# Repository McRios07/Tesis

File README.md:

# Tesis
Repositorio de los archivos de matlab y python de la maestría

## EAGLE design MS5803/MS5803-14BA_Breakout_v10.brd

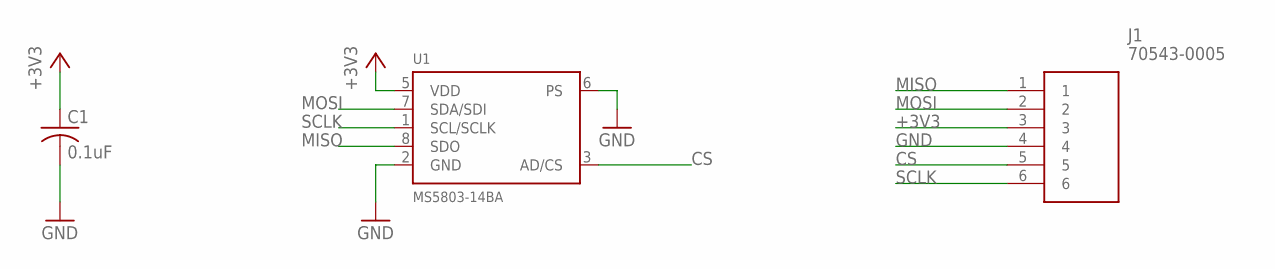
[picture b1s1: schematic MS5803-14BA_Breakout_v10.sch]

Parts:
C1: 0.1uF; C1206
J1: 70543-0005; SHDR6W117P0X254_1X6_1779X508X1
U1: MS5803-14BA; MS5803

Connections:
+3V3: C1.1, J1.3, U1.5 (VDD)
CS: J1.5, U1.3 (AD/CS)
GND: C1.2, J1.4, U1.2 (GND), U1.6 (PS)
MISO: J1.1, U1.8 (SDO)
MOSI: J1.2, U1.7 (SDA/SDI)
SCLK: J1.6, U1.1 (SCL/SCLK)

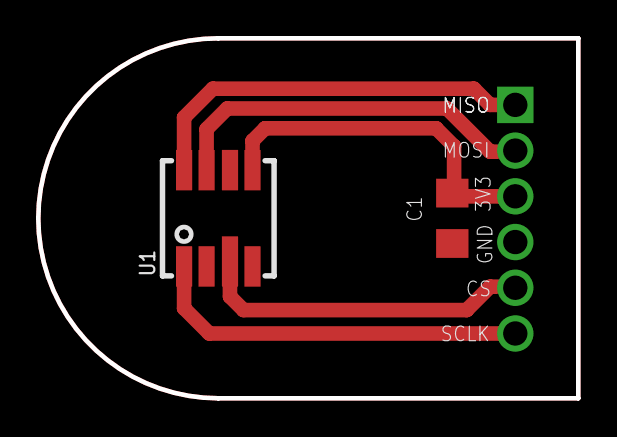
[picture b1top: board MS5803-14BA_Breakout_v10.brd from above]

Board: 2 copper layers, 30.0 x 20.0 mm, 3 parts (1 on the bottom side), 6 nets.

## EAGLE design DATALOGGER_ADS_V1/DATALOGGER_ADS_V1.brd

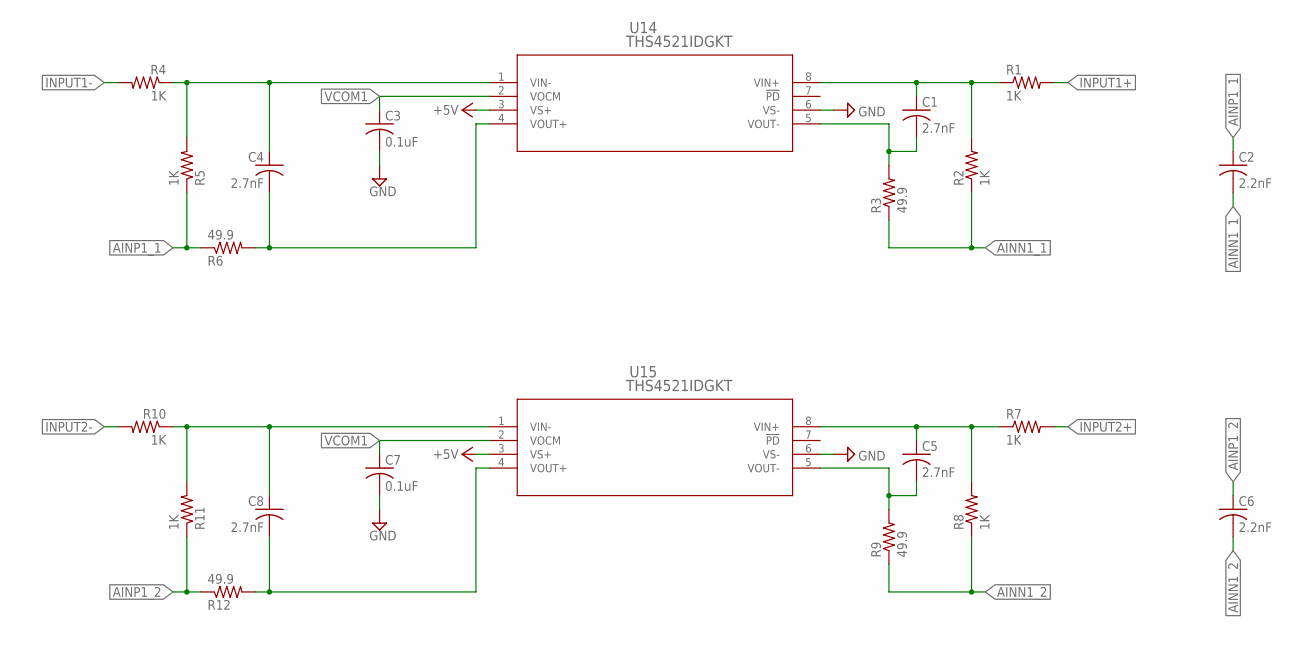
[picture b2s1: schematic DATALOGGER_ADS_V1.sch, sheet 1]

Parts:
C1, C4, C5, C8: 2.7nF; C0603
C2, C6: 2.2nF; C0603
C3, C7: 0.1uF; C0603
R1, R2, R4, R5, R7, R8, R10, R11: 1K; R0603
R3, R6, R9, R12: 49.9; R0603
U14, U15: THS4521IDGKT; DGK8

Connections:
+5V: U14.3 (VS+), U15.3 (VS+); also elsewhere on the board
AINN1_1: C2.2, R2.1, R3.1; also elsewhere on the board
AINN1_2: C6.2, R8.1, R9.1; also elsewhere on the board
AINP1_1: C2.1, R5.1, R6.1; also elsewhere on the board
AINP1_2: C6.1, R11.1, R12.1; also elsewhere on the board
GND: C3.2, C7.2, U14.6 (VS-), U15.6 (VS-); also elsewhere on the board
INPUT1+: R1.2; also elsewhere on the board
INPUT1-: R4.2; also elsewhere on the board
INPUT2+: R7.2; also elsewhere on the board
INPUT2-: R10.2; also elsewhere on the board
unnamed: C4.1, R4.1, R5.2, U14.1 (VIN-)
unnamed: C1.1, R1.1, R2.2, U14.8 (VIN+)
unnamed: C1.2, R3.2, U14.5 (VOUT-)
unnamed: C4.2, R6.2, U14.4 (VOUT+)
unnamed: C5.1, R7.1, R8.2, U15.8 (VIN+)
unnamed: C5.2, R9.2, U15.5 (VOUT-)
unnamed: C8.1, R10.1, R11.2, U15.1 (VIN-)
unnamed: C8.2, R12.2, U15.4 (VOUT+)
VCOM1: C3.1, C7.1, U14.2 (VOCM), U15.2 (VOCM); also elsewhere on the board

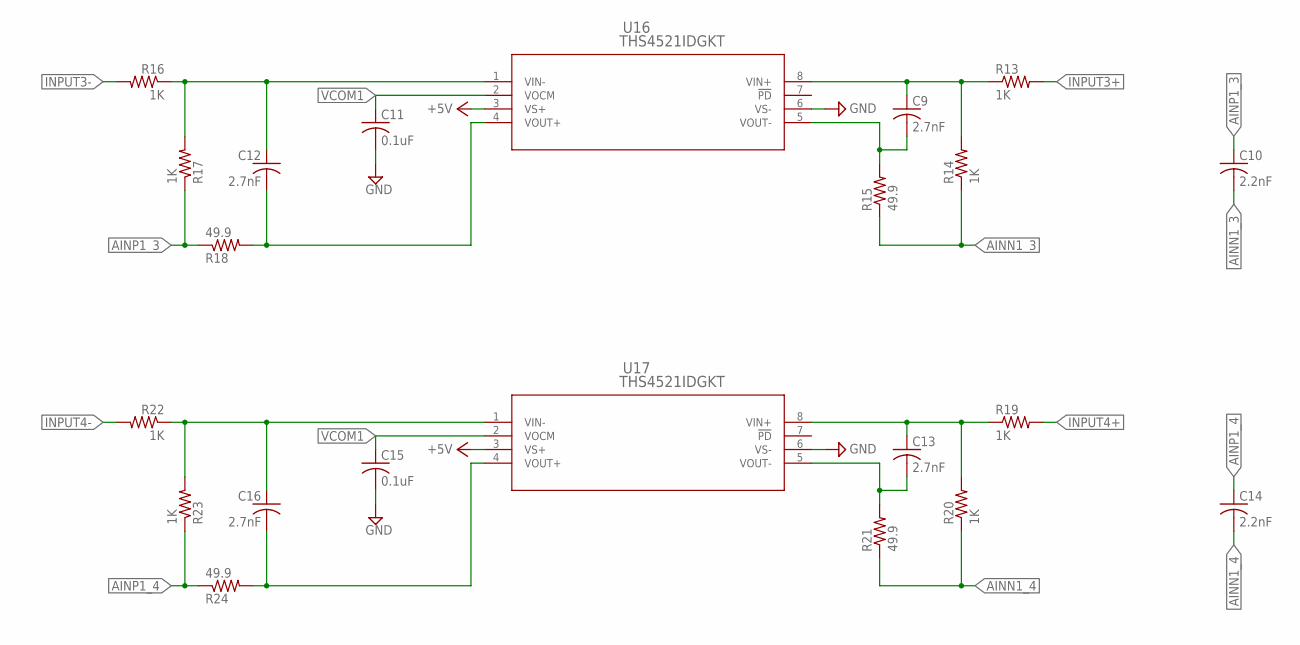
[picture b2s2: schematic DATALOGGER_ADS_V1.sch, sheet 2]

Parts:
C9, C12, C13, C16: 2.7nF; C0603
C10, C14: 2.2nF; C0603
C11, C15: 0.1uF; C0603
R13, R14, R16, R17, R19, R20, R22, R23: 1K; R0603
R15, R18, R21, R24: 49.9; R0603
U16, U17: THS4521IDGKT; DGK8

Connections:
+5V: U16.3 (VS+), U17.3 (VS+); also elsewhere on the board
AINN1_3: C10.2, R14.1, R15.1; also elsewhere on the board
AINN1_4: C14.2, R20.1, R21.1; also elsewhere on the board
AINP1_3: C10.1, R17.1, R18.1; also elsewhere on the board
AINP1_4: C14.1, R23.1, R24.1; also elsewhere on the board
GND: C11.2, C15.2, U16.6 (VS-), U17.6 (VS-); also elsewhere on the board
INPUT3+: R13.2; also elsewhere on the board
INPUT3-: R16.2; also elsewhere on the board
INPUT4+: R19.2; also elsewhere on the board
INPUT4-: R22.2; also elsewhere on the board
unnamed: C9.1, R13.1, R14.2, U16.8 (VIN+)
unnamed: C9.2, R15.2, U16.5 (VOUT-)
unnamed: C12.1, R16.1, R17.2, U16.1 (VIN-)
unnamed: C12.2, R18.2, U16.4 (VOUT+)
unnamed: C13.1, R19.1, R20.2, U17.8 (VIN+)
unnamed: C13.2, R21.2, U17.5 (VOUT-)
unnamed: C16.1, R22.1, R23.2, U17.1 (VIN-)
unnamed: C16.2, R24.2, U17.4 (VOUT+)
VCOM1: C11.1, C15.1, U16.2 (VOCM), U17.2 (VOCM); also elsewhere on the board

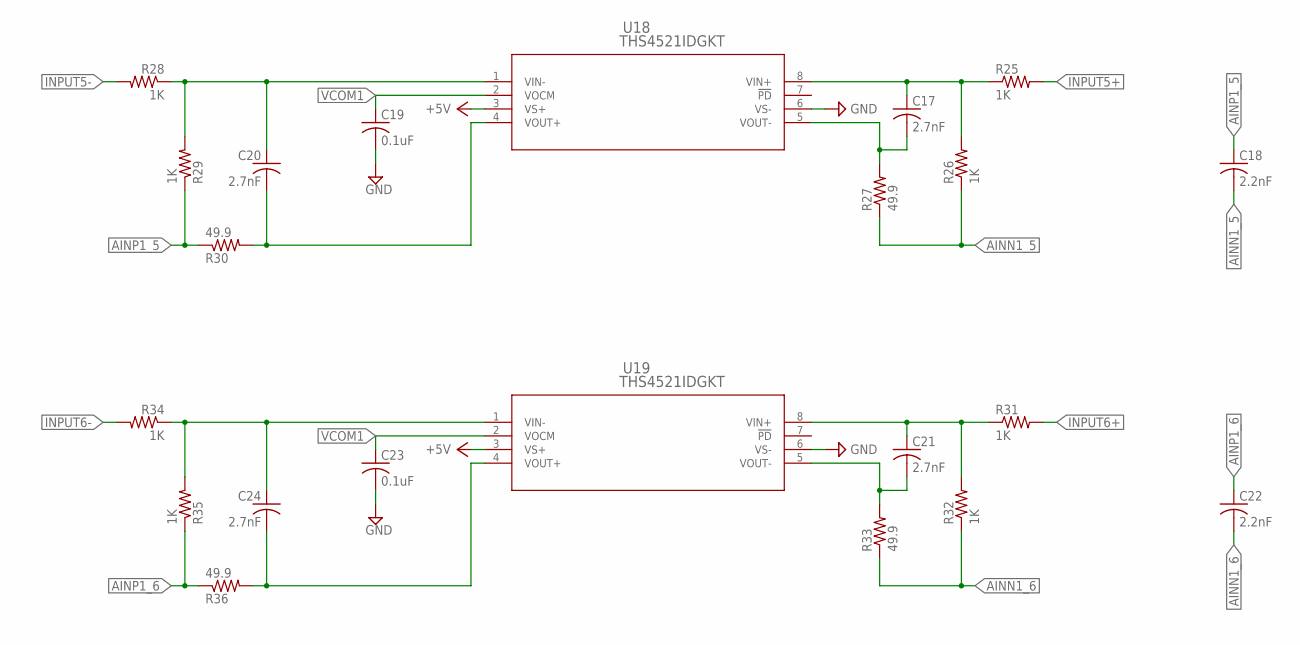
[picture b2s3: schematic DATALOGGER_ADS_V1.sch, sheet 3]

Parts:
C17, C20, C21, C24: 2.7nF; C0603
C18, C22: 2.2nF; C0603
C19, C23: 0.1uF; C0603
R25, R26, R28, R29, R31, R32, R34, R35: 1K; R0603
R27, R30, R33, R36: 49.9; R0603
U18, U19: THS4521IDGKT; DGK8

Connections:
+5V: U18.3 (VS+), U19.3 (VS+); also elsewhere on the board
AINN1_5: C18.2, R26.1, R27.1; also elsewhere on the board
AINN1_6: C22.2, R32.1, R33.1; also elsewhere on the board
AINP1_5: C18.1, R29.1, R30.1; also elsewhere on the board
AINP1_6: C22.1, R35.1, R36.1; also elsewhere on the board
GND: C19.2, C23.2, U18.6 (VS-), U19.6 (VS-); also elsewhere on the board
INPUT5+: R25.2; also elsewhere on the board
INPUT5-: R28.2; also elsewhere on the board
INPUT6+: R31.2; also elsewhere on the board
INPUT6-: R34.2; also elsewhere on the board
unnamed: C17.1, R25.1, R26.2, U18.8 (VIN+)
unnamed: C17.2, R27.2, U18.5 (VOUT-)
unnamed: C20.1, R28.1, R29.2, U18.1 (VIN-)
unnamed: C20.2, R30.2, U18.4 (VOUT+)
unnamed: C21.1, R31.1, R32.2, U19.8 (VIN+)
unnamed: C21.2, R33.2, U19.5 (VOUT-)
unnamed: C24.1, R34.1, R35.2, U19.1 (VIN-)
unnamed: C24.2, R36.2, U19.4 (VOUT+)
VCOM1: C19.1, C23.1, U18.2 (VOCM), U19.2 (VOCM); also elsewhere on the board

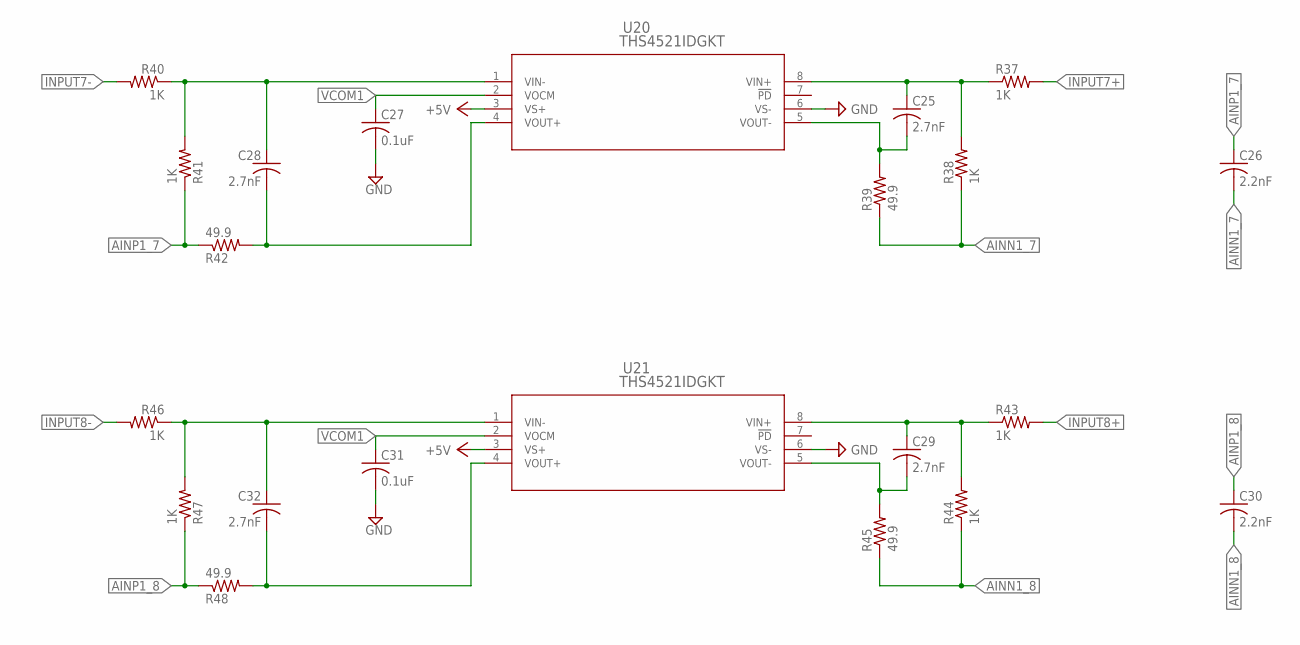
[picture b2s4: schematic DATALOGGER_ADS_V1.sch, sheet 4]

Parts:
C25, C28, C29, C32: 2.7nF; C0603
C26, C30: 2.2nF; C0603
C27, C31: 0.1uF; C0603
R37, R38, R40, R41, R43, R44, R46, R47: 1K; R0603
R39, R42, R45, R48: 49.9; R0603
U20, U21: THS4521IDGKT; DGK8

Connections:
+5V: U20.3 (VS+), U21.3 (VS+); also elsewhere on the board
AINN1_7: C26.2, R38.1, R39.1; also elsewhere on the board
AINN1_8: C30.2, R44.1, R45.1; also elsewhere on the board
AINP1_7: C26.1, R41.1, R42.1; also elsewhere on the board
AINP1_8: C30.1, R47.1, R48.1; also elsewhere on the board
GND: C27.2, C31.2, U20.6 (VS-), U21.6 (VS-); also elsewhere on the board
INPUT7+: R37.2; also elsewhere on the board
INPUT7-: R40.2; also elsewhere on the board
INPUT8+: R43.2; also elsewhere on the board
INPUT8-: R46.2; also elsewhere on the board
unnamed: C25.1, R37.1, R38.2, U20.8 (VIN+)
unnamed: C25.2, R39.2, U20.5 (VOUT-)
unnamed: C28.1, R40.1, R41.2, U20.1 (VIN-)
unnamed: C28.2, R42.2, U20.4 (VOUT+)
unnamed: C29.1, R43.1, R44.2, U21.8 (VIN+)
unnamed: C29.2, R45.2, U21.5 (VOUT-)
unnamed: C32.1, R46.1, R47.2, U21.1 (VIN-)
unnamed: C32.2, R48.2, U21.4 (VOUT+)
VCOM1: C27.1, C31.1, U20.2 (VOCM), U21.2 (VOCM); also elsewhere on the board

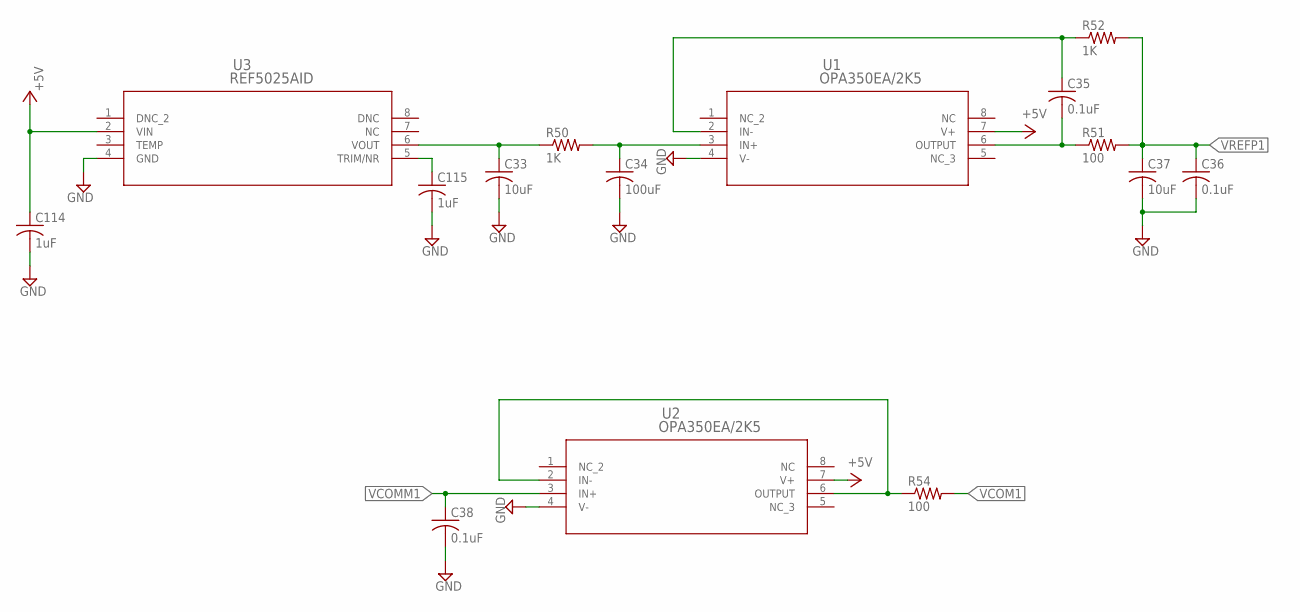
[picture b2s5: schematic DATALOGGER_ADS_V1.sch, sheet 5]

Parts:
C33, C37: 10uF; C0603
C34: 100uF; C1206
C35, C36, C38: 0.1uF; C0603
C114, C115: 1uF; C0603
R50, R52: 1K; R0603
R51, R54: 100; R0603
U1, U2: OPA350EA/2K5; DGK8_TEX
U3: REF5025AID; D8

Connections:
+5V: C114.1, U1.7 (V+), U2.7 (V+), U3.2 (VIN); also elsewhere on the board
GND: C33.2, C34.2, C36.2, C37.2, C38.2, C114.2, C115.2, U1.4 (V-), U2.4 (V-), U3.4 (GND); also elsewhere on the board
unnamed: C34.1, R50.2, U1.3 (IN+)
unnamed: C115.1, U3.5 (TRIM/NR)
unnamed: C33.1, R50.1, U3.6 (VOUT)
unnamed: C35.1, R52.1, U1.2 (IN-)
unnamed: C35.2, R51.1, U1.6 (OUTPUT)
unnamed: R54.1, U2.2 (IN-), U2.6 (OUTPUT)
VCOM1: R54.2; also elsewhere on the board
VCOMM1: C38.1, U2.3 (IN+); also elsewhere on the board
VREFP1: C36.1, C37.1, R51.2, R52.2; also elsewhere on the board

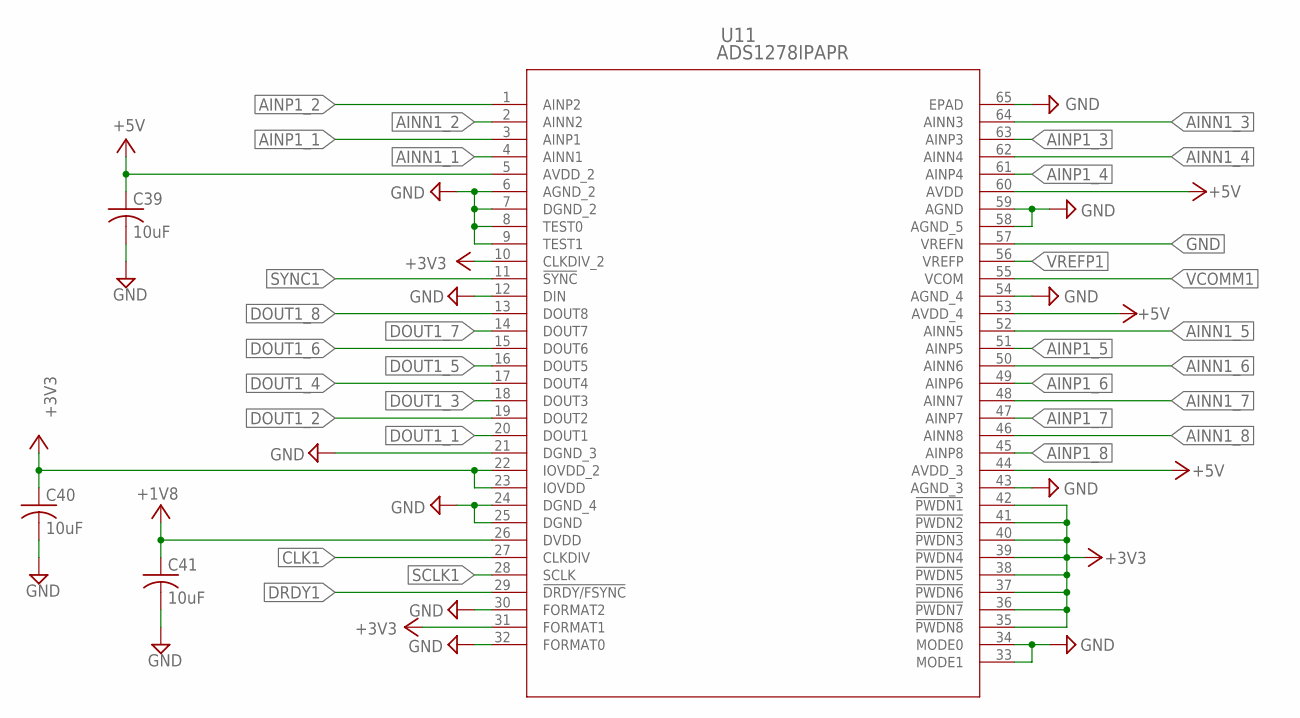
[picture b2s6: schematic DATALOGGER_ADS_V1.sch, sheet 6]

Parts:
C39, C40, C41: 10uF; C0603
U11: ADS1278IPAPR; PAP64_7X7

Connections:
+1V8: C41.1, U11.26 (DVDD); also elsewhere on the board
+3V3: C40.1, U11.10 (CLKDIV_2), U11.22 (IOVDD_2), U11.23 (IOVDD), U11.31 (FORMAT1), U11.35 (!PWDN8), U11.36 (!PWDN7), U11.37 (!PWDN6), U11.38 (!PWDN5), U11.39 (!PWDN4), U11.40 (!PWDN3), U11.41 (!PWDN2), U11.42 (!PWDN1); also elsewhere on the board
+5V: C39.1, U11.5 (AVDD_2), U11.44 (AVDD_3), U11.53 (AVDD_4), U11.60 (AVDD); also elsewhere on the board
AINN1_1: U11.4 (AINN1); also elsewhere on the board
AINN1_2: U11.2 (AINN2); also elsewhere on the board
AINN1_3: U11.64 (AINN3); also elsewhere on the board
AINN1_4: U11.62 (AINN4); also elsewhere on the board
AINN1_5: U11.52 (AINN5); also elsewhere on the board
AINN1_6: U11.50 (AINN6); also elsewhere on the board
AINN1_7: U11.48 (AINN7); also elsewhere on the board
AINN1_8: U11.46 (AINN8); also elsewhere on the board
AINP1_1: U11.3 (AINP1); also elsewhere on the board
AINP1_2: U11.1 (AINP2); also elsewhere on the board
AINP1_3: U11.63 (AINP3); also elsewhere on the board
AINP1_4: U11.61 (AINP4); also elsewhere on the board
AINP1_5: U11.51 (AINP5); also elsewhere on the board
AINP1_6: U11.49 (AINP6); also elsewhere on the board
AINP1_7: U11.47 (AINP7); also elsewhere on the board
AINP1_8: U11.45 (AINP8); also elsewhere on the board
CLK1: U11.27 (CLKDIV); also elsewhere on the board
DOUT1_1: U11.20 (DOUT1); also elsewhere on the board
DOUT1_2: U11.19 (DOUT2); also elsewhere on the board
DOUT1_3: U11.18 (DOUT3); also elsewhere on the board
DOUT1_4: U11.17 (DOUT4); also elsewhere on the board
DOUT1_5: U11.16 (DOUT5); also elsewhere on the board
DOUT1_6: U11.15 (DOUT6); also elsewhere on the board
DOUT1_7: U11.14 (DOUT7); also elsewhere on the board
DOUT1_8: U11.13 (DOUT8); also elsewhere on the board
DRDY1: U11.29 (!DRDY/FSYNC); also elsewhere on the board
GND: C39.2, C40.2, C41.2, U11.6 (AGND_2), U11.7 (DGND_2), U11.8 (TEST0), U11.9 (TEST1), U11.12 (DIN), U11.21 (DGND_3), U11.24 (DGND_4), U11.25 (DGND), U11.30 (FORMAT2), U11.32 (FORMAT0), U11.33 (MODE1), U11.34 (MODE0), U11.43 (AGND_3), U11.54 (AGND_4), U11.57 (VREFN), U11.58 (AGND_5), U11.59 (AGND), U11.65 (EPAD); also elsewhere on the board
SCLK1: U11.28 (SCLK); also elsewhere on the board
SYNC1: U11.11 (!SYNC); also elsewhere on the board
VCOMM1: U11.55 (VCOM); also elsewhere on the board
VREFP1: U11.56 (VREFP); also elsewhere on the board

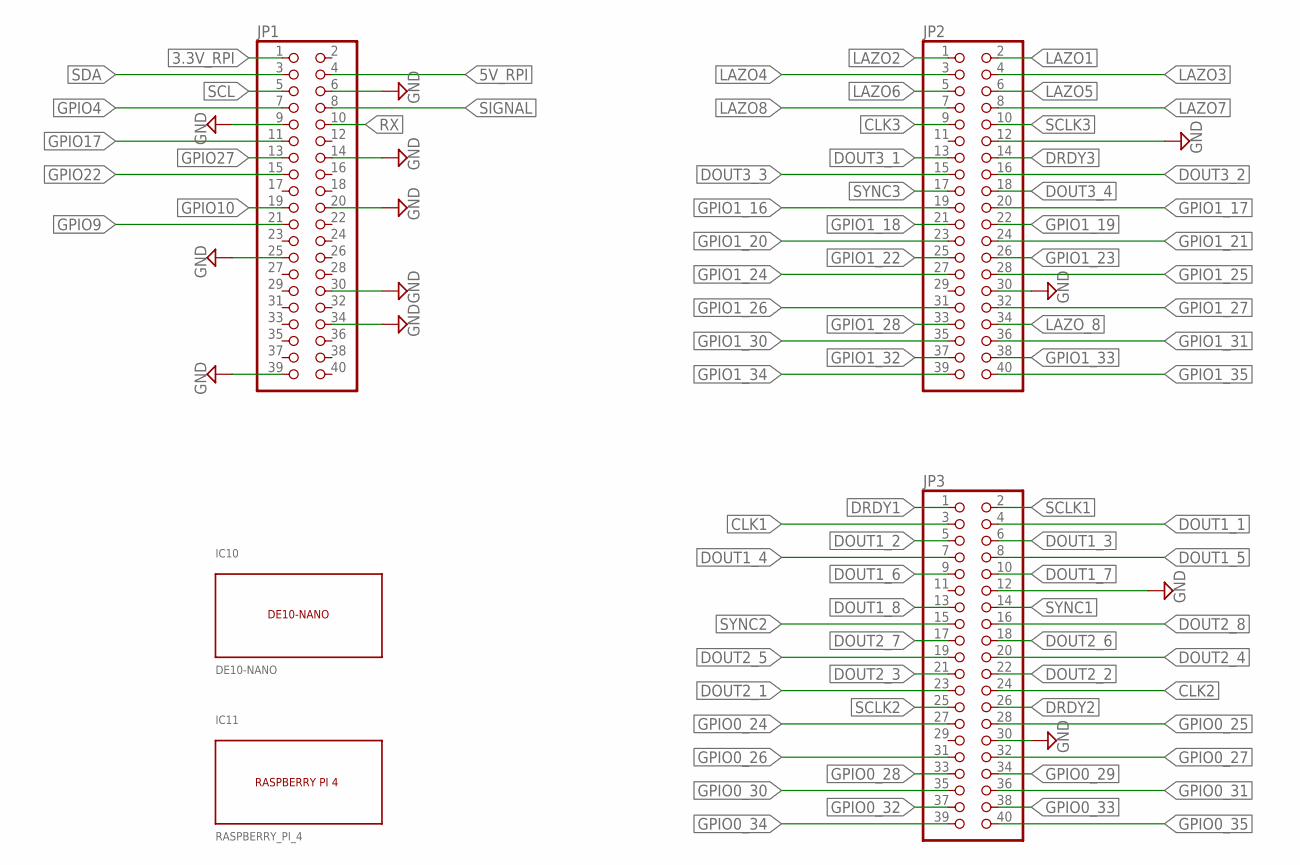
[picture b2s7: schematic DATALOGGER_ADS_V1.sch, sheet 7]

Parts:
IC10: DE10-NANO; DE10_NANO
IC11: RASPBERRY_PI_4
JP1, JP2, JP3: PINHD-2X20; 2X20

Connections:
3.3V_RPI: JP1.1; also elsewhere on the board
5V_RPI: JP1.4; also elsewhere on the board
CLK1: JP3.3; also elsewhere on the board
CLK2: JP3.24; also elsewhere on the board
CLK3: JP2.9; also elsewhere on the board
DOUT1_1: JP3.4; also elsewhere on the board
DOUT1_2: JP3.5; also elsewhere on the board
DOUT1_3: JP3.6; also elsewhere on the board
DOUT1_4: JP3.7; also elsewhere on the board
DOUT1_5: JP3.8; also elsewhere on the board
DOUT1_6: JP3.9; also elsewhere on the board
DOUT1_7: JP3.10; also elsewhere on the board
DOUT1_8: JP3.13; also elsewhere on the board
DOUT2_1: JP3.23; also elsewhere on the board
DOUT2_2: JP3.22; also elsewhere on the board
DOUT2_3: JP3.21; also elsewhere on the board
DOUT2_4: JP3.20; also elsewhere on the board
DOUT2_5: JP3.19; also elsewhere on the board
DOUT2_6: JP3.18; also elsewhere on the board
DOUT2_7: JP3.17; also elsewhere on the board
DOUT2_8: JP3.16; also elsewhere on the board
DOUT3_1: JP2.13; also elsewhere on the board
DOUT3_2: JP2.16; also elsewhere on the board
DOUT3_3: JP2.15; also elsewhere on the board
DOUT3_4: JP2.18; also elsewhere on the board
DRDY1: JP3.1; also elsewhere on the board
DRDY2: JP3.26; also elsewhere on the board
DRDY3: JP2.14; also elsewhere on the board
GND: JP1.6, JP1.9, JP1.14, JP1.20, JP1.25, JP1.30, JP1.34, JP1.39, JP2.12, JP2.30, JP3.12, JP3.30; also elsewhere on the board
GPIO0_24: JP3.27
GPIO0_25: JP3.28
GPIO0_26: JP3.31
GPIO0_27: JP3.32
GPIO0_28: JP3.33
GPIO0_29: JP3.34
GPIO0_30: JP3.35
GPIO0_31: JP3.36
GPIO0_32: JP3.37
GPIO0_33: JP3.38
GPIO0_34: JP3.39
GPIO0_35: JP3.40
GPIO1_16: JP2.19
GPIO1_17: JP2.20
GPIO1_18: JP2.21
GPIO1_19: JP2.22
GPIO1_20: JP2.23
GPIO1_21: JP2.24
GPIO1_22: JP2.25
GPIO1_23: JP2.26
GPIO1_24: JP2.27
GPIO1_25: JP2.28
GPIO1_26: JP2.31
GPIO1_27: JP2.32
GPIO1_28: JP2.33
GPIO1_30: JP2.35
GPIO1_31: JP2.36
GPIO1_32: JP2.37
GPIO1_33: JP2.38
GPIO1_34: JP2.39
GPIO1_35: JP2.40
GPIO4: JP1.7; also elsewhere on the board
GPIO9: JP1.21
GPIO10: JP1.19
GPIO17: JP1.11; also elsewhere on the board
GPIO22: JP1.15; also elsewhere on the board
GPIO27: JP1.13; also elsewhere on the board
LAZO1: JP2.2; also elsewhere on the board
LAZO2: JP2.1; also elsewhere on the board
LAZO3: JP2.4; also elsewhere on the board
LAZO4: JP2.3; also elsewhere on the board
LAZO5: JP2.6; also elsewhere on the board
LAZO6: JP2.5; also elsewhere on the board
LAZO7: JP2.8; also elsewhere on the board
LAZO8: JP2.7; also elsewhere on the board
LAZO_8: JP2.34
RX: JP1.10
SCL: JP1.5; also elsewhere on the board
SCLK1: JP3.2; also elsewhere on the board
SCLK2: JP3.25; also elsewhere on the board
SCLK3: JP2.10; also elsewhere on the board
SDA: JP1.3; also elsewhere on the board
SIGNAL: JP1.8; also elsewhere on the board
SYNC1: JP3.14; also elsewhere on the board
SYNC2: JP3.15; also elsewhere on the board
SYNC3: JP2.17; also elsewhere on the board

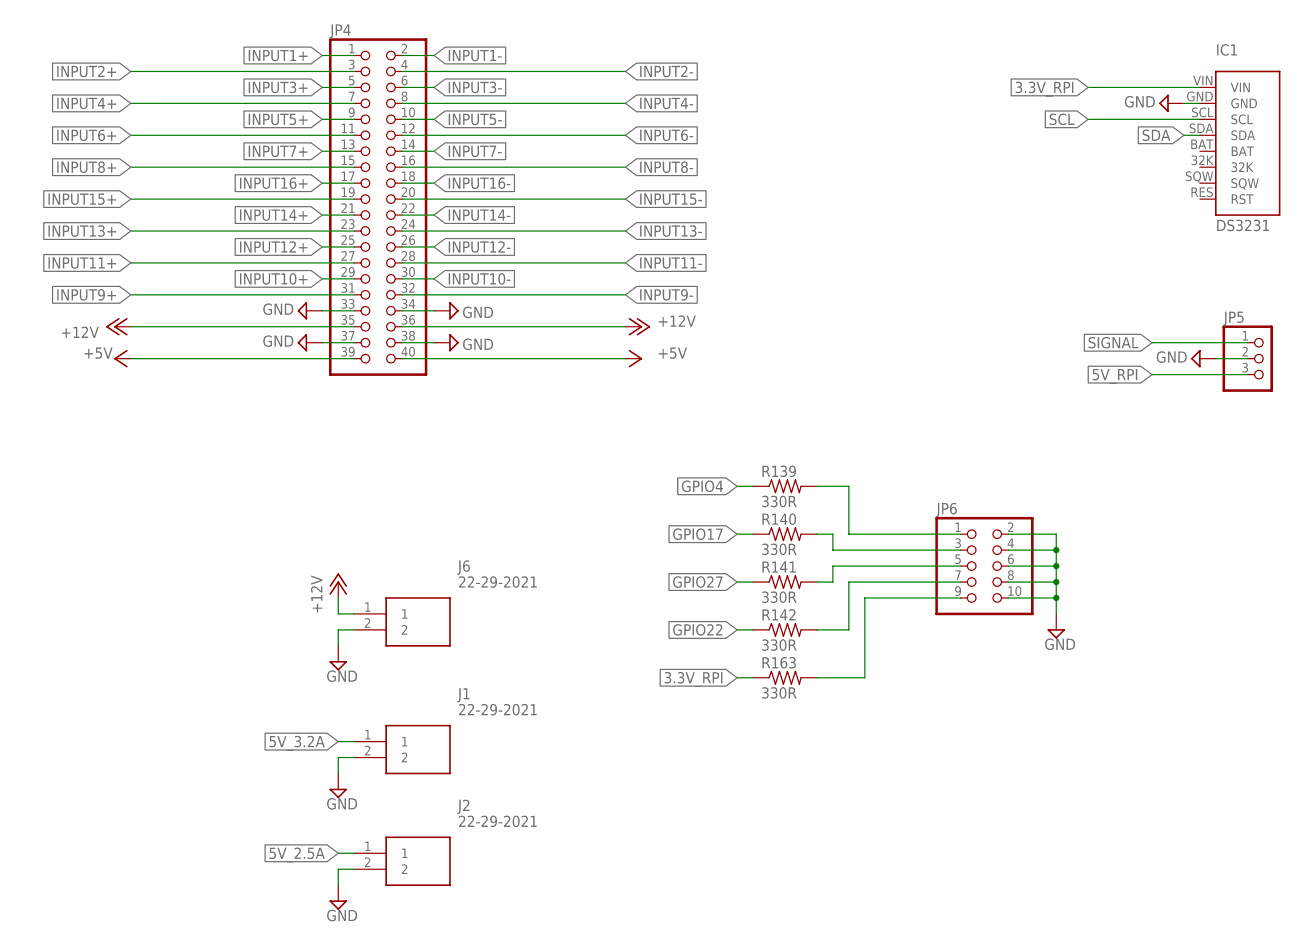
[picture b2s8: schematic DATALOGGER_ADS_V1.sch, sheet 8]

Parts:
IC1: DS3231
J1, J2, J6: 22-29-2021; SHDR2W64P0X254_1X2_508X580X117
JP4: PINHD-2X20; 2X20
JP5: PINHD-1X3; 1X03
JP6: PINHD-2X5; 2X05
R139, R140, R141, R142, R163: 330R; R0603

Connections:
3.3V_RPI: IC1.VIN, R163.1; also elsewhere on the board
5V_2.5A: J2.1; also elsewhere on the board
5V_3.2A: J1.1; also elsewhere on the board
5V_RPI: JP5.3; also elsewhere on the board
+5V: JP4.39, JP4.40; also elsewhere on the board
+12V: J6.1, JP4.35, JP4.36; also elsewhere on the board
GND: IC1.GND, J1.2, J2.2, J6.2, JP4.33, JP4.34, JP4.37, JP4.38, JP5.2, JP6.2, JP6.4, JP6.6, JP6.8, JP6.10; also elsewhere on the board
GPIO4: R139.1; also elsewhere on the board
GPIO17: R140.1; also elsewhere on the board
GPIO22: R142.1; also elsewhere on the board
GPIO27: R141.1; also elsewhere on the board
INPUT1+: JP4.1; also elsewhere on the board
INPUT1-: JP4.2; also elsewhere on the board
INPUT2+: JP4.3; also elsewhere on the board
INPUT2-: JP4.4; also elsewhere on the board
INPUT3+: JP4.5; also elsewhere on the board
INPUT3-: JP4.6; also elsewhere on the board
INPUT4+: JP4.7; also elsewhere on the board
INPUT4-: JP4.8; also elsewhere on the board
INPUT5+: JP4.9; also elsewhere on the board
INPUT5-: JP4.10; also elsewhere on the board
INPUT6+: JP4.11; also elsewhere on the board
INPUT6-: JP4.12; also elsewhere on the board
INPUT7+: JP4.13; also elsewhere on the board
INPUT7-: JP4.14; also elsewhere on the board
INPUT8+: JP4.15; also elsewhere on the board
INPUT8-: JP4.16; also elsewhere on the board
INPUT9+: JP4.31; also elsewhere on the board
INPUT9-: JP4.32; also elsewhere on the board
INPUT10+: JP4.29; also elsewhere on the board
INPUT10-: JP4.30; also elsewhere on the board
INPUT11+: JP4.27; also elsewhere on the board
INPUT11-: JP4.28; also elsewhere on the board
INPUT12+: JP4.25; also elsewhere on the board
INPUT12-: JP4.26; also elsewhere on the board
INPUT13+: JP4.23; also elsewhere on the board
INPUT13-: JP4.24; also elsewhere on the board
INPUT14+: JP4.21; also elsewhere on the board
INPUT14-: JP4.22; also elsewhere on the board
INPUT15+: JP4.19; also elsewhere on the board
INPUT15-: JP4.20; also elsewhere on the board
INPUT16+: JP4.17; also elsewhere on the board
INPUT16-: JP4.18; also elsewhere on the board
unnamed: JP6.9, R163.2
unnamed: JP6.1, R139.2
unnamed: JP6.3, R140.2
unnamed: JP6.5, R141.2
unnamed: JP6.7, R142.2
SCL: IC1.SCL; also elsewhere on the board
SDA: IC1.SDA; also elsewhere on the board
SIGNAL: JP5.1; also elsewhere on the board

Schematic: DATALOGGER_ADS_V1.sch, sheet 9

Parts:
C42, C45, C46, C49: 2.7nF; C0603
C43, C47: 2.2nF; C0603
C44, C48: 0.1uF; C0603
R55, R56, R58, R59, R61, R62, R64, R65: 1K; R0603
R57, R60, R63, R66: 49.9; R0603
U22, U23: THS4521IDGKT; DGK8

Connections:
+5V: U22.3 (VS+), U23.3 (VS+); also elsewhere on the board
AINN2_1: C43.2, R56.1, R57.1; also elsewhere on the board
AINN2_2: C47.2, R62.1, R63.1; also elsewhere on the board
AINP2_1: C43.1, R59.1, R60.1; also elsewhere on the board
AINP2_2: C47.1, R65.1, R66.1; also elsewhere on the board
GND: C44.2, C48.2, U22.6 (VS-), U23.6 (VS-); also elsewhere on the board
INPUT9+: R55.2; also elsewhere on the board
INPUT9-: R58.2; also elsewhere on the board
INPUT10+: R61.2; also elsewhere on the board
INPUT10-: R64.2; also elsewhere on the board
unnamed: C42.1, R55.1, R56.2, U22.8 (VIN+)
unnamed: C42.2, R57.2, U22.5 (VOUT-)
unnamed: C45.1, R58.1, R59.2, U22.1 (VIN-)
unnamed: C45.2, R60.2, U22.4 (VOUT+)
unnamed: C46.1, R61.1, R62.2, U23.8 (VIN+)
unnamed: C46.2, R63.2, U23.5 (VOUT-)
unnamed: C49.1, R64.1, R65.2, U23.1 (VIN-)
unnamed: C49.2, R66.2, U23.4 (VOUT+)
VCOM2: C44.1, C48.1, U22.2 (VOCM), U23.2 (VOCM); also elsewhere on the board

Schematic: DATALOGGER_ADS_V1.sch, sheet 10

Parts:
C50, C53, C54, C57: 2.7nF; C0603
C51, C55: 2.2nF; C0603
C52, C56: 0.1uF; C0603
R67, R68, R70, R71, R73, R74, R76, R77: 1K; R0603
R69, R72, R75, R78: 49.9; R0603
U24, U25: THS4521IDGKT; DGK8

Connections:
+5V: U24.3 (VS+), U25.3 (VS+); also elsewhere on the board
AINN2_3: C51.2, R68.1, R69.1; also elsewhere on the board
AINN2_4: C55.2, R74.1, R75.1; also elsewhere on the board
AINP2_3: C51.1, R71.1, R72.1; also elsewhere on the board
AINP2_4: C55.1, R77.1, R78.1; also elsewhere on the board
GND: C52.2, C56.2, U24.6 (VS-), U25.6 (VS-); also elsewhere on the board
INPUT11+: R67.2; also elsewhere on the board
INPUT11-: R70.2; also elsewhere on the board
INPUT12+: R73.2; also elsewhere on the board
INPUT12-: R76.2; also elsewhere on the board
unnamed: C50.1, R67.1, R68.2, U24.8 (VIN+)
unnamed: C50.2, R69.2, U24.5 (VOUT-)
unnamed: C53.1, R70.1, R71.2, U24.1 (VIN-)
unnamed: C53.2, R72.2, U24.4 (VOUT+)
unnamed: C54.1, R73.1, R74.2, U25.8 (VIN+)
unnamed: C54.2, R75.2, U25.5 (VOUT-)
unnamed: C57.1, R76.1, R77.2, U25.1 (VIN-)
unnamed: C57.2, R78.2, U25.4 (VOUT+)
VCOM2: C52.1, C56.1, U24.2 (VOCM), U25.2 (VOCM); also elsewhere on the board

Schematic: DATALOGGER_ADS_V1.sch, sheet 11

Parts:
C58, C61, C62, C65: 2.7nF; C0603
C59, C63: 2.2nF; C0603
C60, C64: 0.1uF; C0603
R79, R80, R82, R83, R85, R86, R88, R89: 1K; R0603
R81, R84, R87, R90: 49.9; R0603
U26, U27: THS4521IDGKT; DGK8

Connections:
+5V: U26.3 (VS+), U27.3 (VS+); also elsewhere on the board
AINN2_5: C59.2, R80.1, R81.1; also elsewhere on the board
AINN2_6: C63.2, R86.1, R87.1; also elsewhere on the board
AINP2_5: C59.1, R83.1, R84.1; also elsewhere on the board
AINP2_6: C63.1, R89.1, R90.1; also elsewhere on the board
GND: C60.2, C64.2, U26.6 (VS-), U27.6 (VS-); also elsewhere on the board
INPUT13+: R79.2; also elsewhere on the board
INPUT13-: R82.2; also elsewhere on the board
INPUT14+: R85.2; also elsewhere on the board
INPUT14-: R88.2; also elsewhere on the board
unnamed: C58.1, R79.1, R80.2, U26.8 (VIN+)
unnamed: C58.2, R81.2, U26.5 (VOUT-)
unnamed: C61.1, R82.1, R83.2, U26.1 (VIN-)
unnamed: C61.2, R84.2, U26.4 (VOUT+)
unnamed: C62.1, R85.1, R86.2, U27.8 (VIN+)
unnamed: C62.2, R87.2, U27.5 (VOUT-)
unnamed: C65.1, R88.1, R89.2, U27.1 (VIN-)
unnamed: C65.2, R90.2, U27.4 (VOUT+)
VCOM2: C60.1, C64.1, U26.2 (VOCM), U27.2 (VOCM); also elsewhere on the board

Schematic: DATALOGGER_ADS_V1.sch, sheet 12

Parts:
C66, C69, C70, C73: 2.7nF; C0603
C67, C71: 2.2nF; C0603
C68, C72: 0.1uF; C0603
R91, R92, R94, R95, R97, R98, R100, R101: 1K; R0603
R93, R96, R99, R102: 49.9; R0603
U28, U29: THS4521IDGKT; DGK8

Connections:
+5V: U28.3 (VS+), U29.3 (VS+); also elsewhere on the board
AINN2_7: C67.2, R92.1, R93.1; also elsewhere on the board
AINN2_8: C71.2, R98.1, R99.1; also elsewhere on the board
AINP2_7: C67.1, R95.1, R96.1; also elsewhere on the board
AINP2_8: C71.1, R101.1, R102.1; also elsewhere on the board
GND: C68.2, C72.2, U28.6 (VS-), U29.6 (VS-); also elsewhere on the board
INPUT15+: R91.2; also elsewhere on the board
INPUT15-: R94.2; also elsewhere on the board
INPUT16+: R97.2; also elsewhere on the board
INPUT16-: R100.2; also elsewhere on the board
unnamed: C66.1, R91.1, R92.2, U28.8 (VIN+)
unnamed: C66.2, R93.2, U28.5 (VOUT-)
unnamed: C69.1, R94.1, R95.2, U28.1 (VIN-)
unnamed: C69.2, R96.2, U28.4 (VOUT+)
unnamed: C70.1, R97.1, R98.2, U29.8 (VIN+)
unnamed: C70.2, R99.2, U29.5 (VOUT-)
unnamed: C73.1, R100.1, R101.2, U29.1 (VIN-)
unnamed: C73.2, R102.2, U29.4 (VOUT+)
VCOM2: C68.1, C72.1, U28.2 (VOCM), U29.2 (VOCM); also elsewhere on the board

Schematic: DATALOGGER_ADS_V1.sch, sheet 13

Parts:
C74, C78: 10uF; C0603
C75: 100uF; C1206
C76, C77, C79: 0.1uF; C0603
C118, C119: 1uF; C0603
R104, R106: 1K; R0603
R105, R108: 100; R0603
U4, U5: OPA350EA/2K5; DGK8_TEX
U13: REF5025AID; D8

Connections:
+5V: C119.1, U4.7 (V+), U5.7 (V+), U13.2 (VIN); also elsewhere on the board
GND: C74.2, C75.2, C77.2, C78.2, C79.2, C118.2, C119.2, U4.4 (V-), U5.4 (V-), U13.4 (GND); also elsewhere on the board
unnamed: C75.1, R104.2, U4.3 (IN+)
unnamed: C74.1, R104.1, U13.6 (VOUT)
unnamed: C118.1, U13.5 (TRIM/NR)
unnamed: C76.1, R106.1, U4.2 (IN-)
unnamed: C76.2, R105.1, U4.6 (OUTPUT)
unnamed: R108.1, U5.2 (IN-), U5.6 (OUTPUT)
VCOM2: R108.2; also elsewhere on the board
VCOMM2: C79.1, U5.3 (IN+); also elsewhere on the board
VREFP2: C77.1, C78.1, R105.2, R106.2; also elsewhere on the board

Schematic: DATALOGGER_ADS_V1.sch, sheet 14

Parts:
C80, C81, C82: 10uF; C0603
U6: ADS1278IPAPR; PAP64_7X7

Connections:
+1V8: C82.1, U6.26 (DVDD); also elsewhere on the board
+3V3: C81.1, U6.10 (CLKDIV_2), U6.22 (IOVDD_2), U6.23 (IOVDD), U6.31 (FORMAT1), U6.35 (!PWDN8), U6.36 (!PWDN7), U6.37 (!PWDN6), U6.38 (!PWDN5), U6.39 (!PWDN4), U6.40 (!PWDN3), U6.41 (!PWDN2), U6.42 (!PWDN1); also elsewhere on the board
+5V: C80.1, U6.5 (AVDD_2), U6.44 (AVDD_3), U6.53 (AVDD_4), U6.60 (AVDD); also elsewhere on the board
AINN2_1: U6.4 (AINN1); also elsewhere on the board
AINN2_2: U6.2 (AINN2); also elsewhere on the board
AINN2_3: U6.64 (AINN3); also elsewhere on the board
AINN2_4: U6.62 (AINN4); also elsewhere on the board
AINN2_5: U6.52 (AINN5); also elsewhere on the board
AINN2_6: U6.50 (AINN6); also elsewhere on the board
AINN2_7: U6.48 (AINN7); also elsewhere on the board
AINN2_8: U6.46 (AINN8); also elsewhere on the board
AINP2_1: U6.3 (AINP1); also elsewhere on the board
AINP2_2: U6.1 (AINP2); also elsewhere on the board
AINP2_3: U6.63 (AINP3); also elsewhere on the board
AINP2_4: U6.61 (AINP4); also elsewhere on the board
AINP2_5: U6.51 (AINP5); also elsewhere on the board
AINP2_6: U6.49 (AINP6); also elsewhere on the board
AINP2_7: U6.47 (AINP7); also elsewhere on the board
AINP2_8: U6.45 (AINP8); also elsewhere on the board
CLK2: U6.27 (CLKDIV); also elsewhere on the board
DOUT2_1: U6.20 (DOUT1); also elsewhere on the board
DOUT2_2: U6.19 (DOUT2); also elsewhere on the board
DOUT2_3: U6.18 (DOUT3); also elsewhere on the board
DOUT2_4: U6.17 (DOUT4); also elsewhere on the board
DOUT2_5: U6.16 (DOUT5); also elsewhere on the board
DOUT2_6: U6.15 (DOUT6); also elsewhere on the board
DOUT2_7: U6.14 (DOUT7); also elsewhere on the board
DOUT2_8: U6.13 (DOUT8); also elsewhere on the board
DRDY2: U6.29 (!DRDY/FSYNC); also elsewhere on the board
GND: C80.2, C81.2, C82.2, U6.6 (AGND_2), U6.7 (DGND_2), U6.8 (TEST0), U6.9 (TEST1), U6.12 (DIN), U6.21 (DGND_3), U6.24 (DGND_4), U6.25 (DGND), U6.30 (FORMAT2), U6.32 (FORMAT0), U6.33 (MODE1), U6.34 (MODE0), U6.43 (AGND_3), U6.54 (AGND_4), U6.57 (VREFN), U6.58 (AGND_5), U6.59 (AGND), U6.65 (EPAD); also elsewhere on the board
SCLK2: U6.28 (SCLK); also elsewhere on the board
SYNC2: U6.11 (!SYNC); also elsewhere on the board
VCOMM2: U6.55 (VCOM); also elsewhere on the board
VREFP2: U6.56 (VREFP); also elsewhere on the board

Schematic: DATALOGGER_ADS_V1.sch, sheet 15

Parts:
C83, C86, C87, C90: 2.7nF; C0603
C84, C88: 2.2nF; C0603
C85, C89: 0.1uF; C0603
R109, R110, R112, R113, R115, R116, R118, R119: 1K; R0603
R111, R114, R117, R120: 49.9; R0603
U30, U31: THS4521IDGKT; DGK8

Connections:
+5V: U30.3 (VS+), U31.3 (VS+); also elsewhere on the board
AINN3_1: C84.2, R110.1, R111.1; also elsewhere on the board
AINN3_2: C88.2, R116.1, R117.1; also elsewhere on the board
AINP3_1: C84.1, R113.1, R114.1; also elsewhere on the board
AINP3_2: C88.1, R119.1, R120.1; also elsewhere on the board
GND: C85.2, C89.2, R112.2, R118.2, U30.6 (VS-), U31.6 (VS-); also elsewhere on the board
INPUT17+: R109.2; also elsewhere on the board
INPUT18+: R115.2; also elsewhere on the board
unnamed: C83.1, R109.1, R110.2, U30.8 (VIN+)
unnamed: C83.2, R111.2, U30.5 (VOUT-)
unnamed: C86.1, R112.1, R113.2, U30.1 (VIN-)
unnamed: C86.2, R114.2, U30.4 (VOUT+)
unnamed: C87.1, R115.1, R116.2, U31.8 (VIN+)
unnamed: C87.2, R117.2, U31.5 (VOUT-)
unnamed: C90.1, R118.1, R119.2, U31.1 (VIN-)
unnamed: C90.2, R120.2, U31.4 (VOUT+)
VCOM3: C85.1, C89.1, U30.2 (VOCM), U31.2 (VOCM); also elsewhere on the board

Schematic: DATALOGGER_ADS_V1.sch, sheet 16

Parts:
C91, C94, C95, C98: 2.7nF; C0603
C92, C96: 2.2nF; C0603
C93, C97: 0.1uF; C0603
R121, R122, R124, R125, R127, R128, R130, R131: 1K; R0603
R123, R126, R129, R132: 49.9; R0603
U32, U33: THS4521IDGKT; DGK8

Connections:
+5V: U32.3 (VS+), U33.3 (VS+); also elsewhere on the board
AINN3_3: C92.2, R122.1, R123.1; also elsewhere on the board
AINN3_4: C96.2, R128.1, R129.1; also elsewhere on the board
AINP3_3: C92.1, R125.1, R126.1; also elsewhere on the board
AINP3_4: C96.1, R131.1, R132.1; also elsewhere on the board
GND: C93.2, C97.2, R124.2, R130.2, U32.6 (VS-), U33.6 (VS-); also elsewhere on the board
INPUT19+: R121.2; also elsewhere on the board
INPUT20+: R127.2; also elsewhere on the board
unnamed: C91.1, R121.1, R122.2, U32.8 (VIN+)
unnamed: C91.2, R123.2, U32.5 (VOUT-)
unnamed: C94.1, R124.1, R125.2, U32.1 (VIN-)
unnamed: C94.2, R126.2, U32.4 (VOUT+)
unnamed: C95.1, R127.1, R128.2, U33.8 (VIN+)
unnamed: C95.2, R129.2, U33.5 (VOUT-)
unnamed: C98.1, R130.1, R131.2, U33.1 (VIN-)
unnamed: C98.2, R132.2, U33.4 (VOUT+)
VCOM3: C93.1, C97.1, U32.2 (VOCM), U33.2 (VOCM); also elsewhere on the board

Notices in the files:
parts and their libraries:
COPYRIGHT: Copyright (C) 2018 Accelerated Designs. All rights reserved
COPYRIGHT: Copyright (C) 2016 Accelerated Designs. All rights reserved
